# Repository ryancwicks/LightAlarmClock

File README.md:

# LightAlarmClock

Design (software and hardware) for a light alarm clock with a web interface for control.

[Documentation Site](https://ryancwicks.github.io/LightAlarmClock/)

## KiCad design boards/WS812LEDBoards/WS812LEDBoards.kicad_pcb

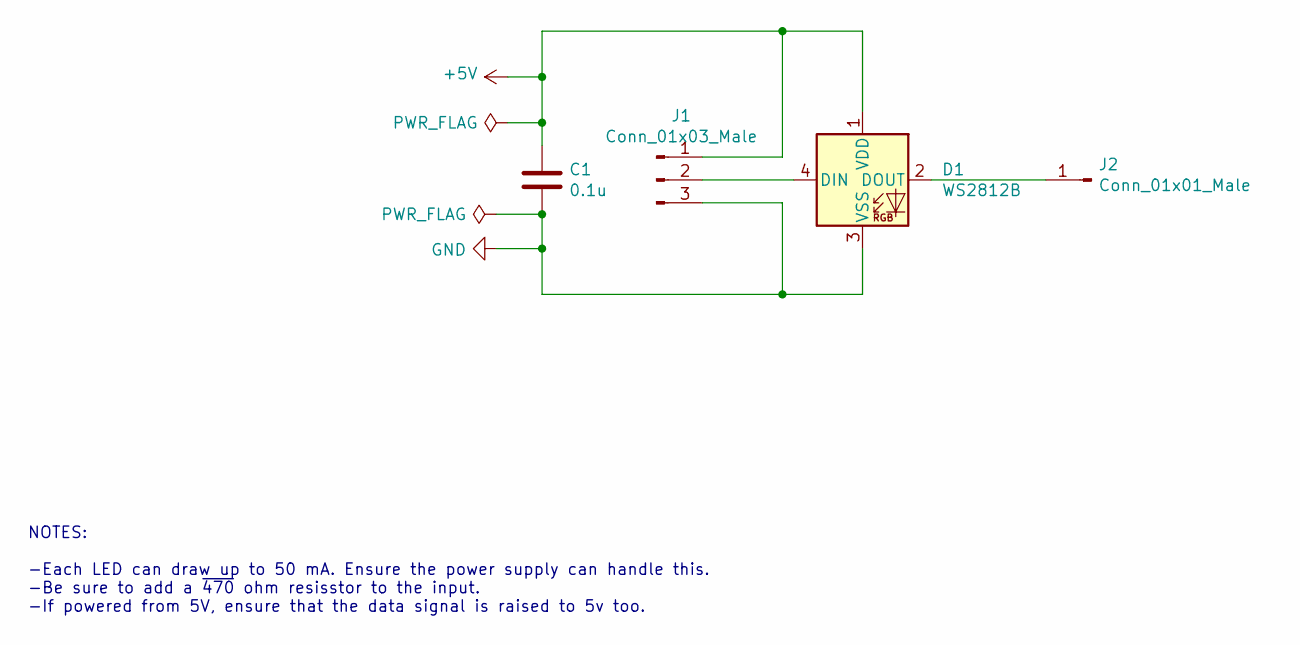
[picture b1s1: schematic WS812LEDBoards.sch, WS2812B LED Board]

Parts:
C1: 0.1u; C_0603_1608Metric_Pad1.05x0.95mm_HandSolder
D1: WS2812B; LED_WS2812B_PLCC4_5.0x5.0mm_P3.2mm
J1: Conn_01x03_Male; PinHeader_1x03_P2.54mm_Vertical
J2: Conn_01x01_Male; PinHeader_1x01_P2.54mm_Vertical

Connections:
+5V: C1.1, D1.1 (VDD), J1.1
GND: C1.2, D1.3 (VSS), J1.3
unnamed: D1.2 (DOUT), J2.1
unnamed: D1.4 (DIN), J1.2

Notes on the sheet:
NOTES: -Each LED can draw up to 50 mA. Ensure the power supply can handle this. -Be sure to add a ~470 ohm resisstor to the input. -If powered from 5V, ensure that the data signal is raised to 5v too.

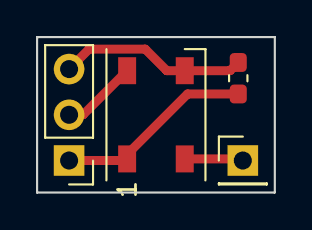
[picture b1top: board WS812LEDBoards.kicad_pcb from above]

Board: 2 copper layers, 13.2 x 8.6 mm, 4 parts (0 on the bottom side), 4 nets.

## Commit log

2019-06-12 Initial work on page.
2019-06-13 Setting up css and JS for top of page.
2019-06-13 Added resizing for small screens.
2019-06-13 fonts in nav bar
2019-06-14 Added test web server. Started to add page drawing functions.
2019-06-14 Started adding prototype methods for the page class.
2019-06-18 Started adding clock and time objects.
2019-06-28 Added led boards.
2019-06-28 Added WS2812B breakout board.
2019-06-28 started work on other board.
2019-07-02 Started adding documentation to the project.
2019-07-02 Added initial notes to the ESP32 description.
2019-07-02 Updated docs to show working ESP32
2019-07-24 Added new page for the Eink display
2019-07-24 Updated readme.
2019-07-24 Documented getting the e-ink working.
2019-07-24 reduced image size in e-ink documentation.
2019-09-03 Added more documentation and a lot of firmware. Display, LED, WIFI and storage modules are now all included, and I'm not filling up memory yet.
2019-11-01 Added a setup interface.
2019-11-01 started to add json messages.
